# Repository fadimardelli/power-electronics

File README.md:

# Power Electronics

Lab coursework and project for *Power Electronics*, KU Leuven (Campus Group T) — Master's in Electronics-ICT Engineering Technology. The labs are hands-on: build the circuit on a breadboard, characterize it with a bench power supply and oscilloscope, and report the measured behavior against the theoretical prediction.

## Labs

| Lab | Topic | Status |
|---|---|---|
| [`lab-1`](./lab-1) | Thyristor, TRIAC, MOSFET/IGBT switching & clamping circuits | Done |
| [`lab-3`](./lab-3) | Charge pump power supplies (LT1054) & step-down converter (LM2575) | Done |

## Project

| Project | Topic | Status |
|---|---|---|
| [`project`](./project) | DC-DC heavy vehicle converter (24V→12V, 5A) — design, PCB, bench validation | Done |

## Author

Fadi Mardelli — labs done in pairs as noted per lab.

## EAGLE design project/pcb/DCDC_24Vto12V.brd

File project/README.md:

# DC-DC Heavy Vehicle Converter (24 V → 12 V, 5 A)

**Course:** Power Electronics, KU Leuven — Lab responsible: Gert Van Loock
**Team:** Fadi Mardelli, Marios Vlachos

## Goal

Design, build, and characterize a working power-supply prototype from scratch — this is the course's capstone project, distinct from the weekly labs. The brief: pick a converter application from a shortlist (battery chargers, USB supplies, vehicle converters, etc.), design the topology and component values, get a PCB fabricated and soldered, and validate it on the bench against the design targets. A full technical report and a live demo of the working prototype were both required deliverables.

This team's chosen application: a **heavy-vehicle DC-DC converter** converting a 24 V input (regulated over a 20–28 V range) down to a stable 12 V output at up to 5 A, targeting **>90% efficiency**.

## Design

- **Topology:** synchronous buck (step-down) converter — chosen for simplicity and its efficiency advantage over buck-boost or flyback topologies in a pure step-down application.
- **Controller IC:** TI **LM3150** wide-V<sub>IN</sub> synchronous buck controller (6–42 V input range, Constant On-Time control, integrated current limiting / short-circuit / thermal protection).
- **Component values** (R<sub>fb1</sub>/R<sub>fb2</sub>, R<sub>on</sub>, inductor, input/output capacitors, feed-forward and soft-start capacitors, MOSFETs) were hand-calculated from the LM3150 datasheet procedure, then cross-checked against TI's WEBENCH power design tool. Final switching frequency: 500 kHz.
- **PCB:** 2-layer board with short gate-drive traces and a minimized switch-node copper area to control EMI, laid out in EAGLE (exported from WEBENCH, then customized).
- Components were sourced from Farnell (EU stock, single-quantity purchasing).

## Repository contents

```
project/
├── Report_HeavyVehicleConverter.pdf   # Full technical report
├── schematic/DCDC_24Vto12V.sch         # EAGLE schematic
├── pcb/DCDC_24Vto12V.brd               # EAGLE board layout
├── data/Measurements.xlsx              # Raw bench measurement data
└── images/
    ├── PCB_Microscope_Photo.jpg         # Close-up of the assembled board
    ├── Vout_Ripple_200Ohm.JPG           # Output ripple capture
    ├── Vswitch_Switch_Time.JPG          # Switch-node rise-time capture
    ├── static_load_sweep/               # Input-voltage sweep (20–28 V) at 200Ω load
    └── dynamic_load/                    # Load-transient response captures (100 kHz / 250 kHz)
```

The LM2677 datasheet and TI's WEBENCH notice bundled in the original project package are left out, as neither is this team's own work.

## Results

| Metric | Target | Measured |
|---|---|---|
| Output voltage | 12 V | ~12.6–12.7 V, stable across 0–2.1 A load and 20–28 V input |
| Efficiency | >90% | **94.2%** peak (95% simulated) |
| Switching frequency | 500 kHz (design) | ~630 kHz measured |
| Output ripple | — | 34 mV<sub>pp</sub> at 2.5 MHz |
| Switch-node rise time | — | ~17.6 ns |
| IC / MOSFET temperature (5 min, 200 Ω load) | below 165 °C shutdown | 44.1 °C / 40.9 °C |

The converter held continuous-conduction-mode operation at moderate-to-heavy load, with a duty cycle matching theoretical prediction (~53% at V<sub>in</sub> = 24 V). Dynamic load testing (10 V, 100–250 kHz square wave) showed the expected overshoot-on-unload / undershoot-on-load behavior, with some unexpected ringing on overshoot — noted in the report as a possible feedback-compensation improvement for a future revision.

Full derivations, the bill of materials, and the complete measurement set are in the [report](./Report_HeavyVehicleConverter.pdf).

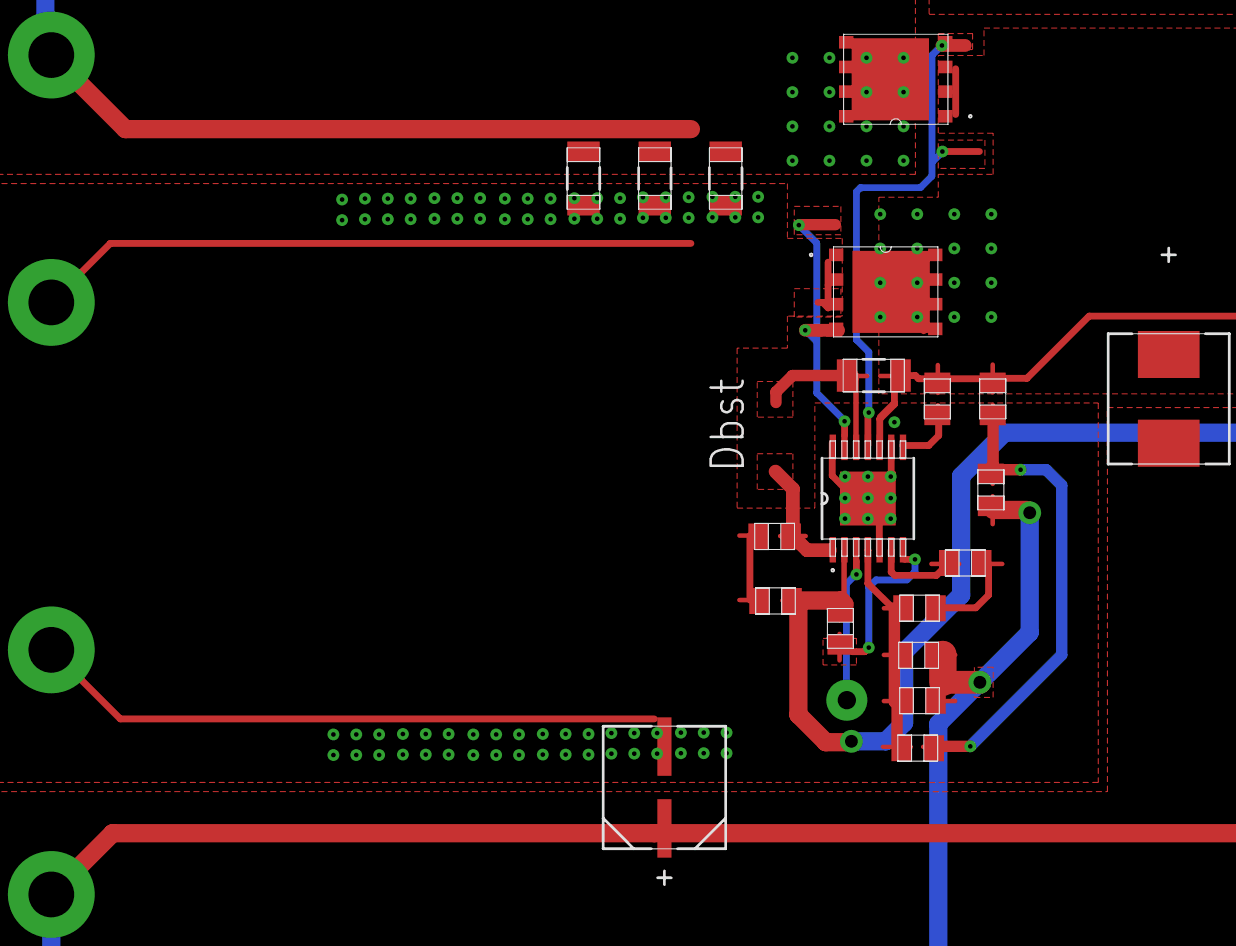
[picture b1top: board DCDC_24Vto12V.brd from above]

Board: 4 copper layers, 25 parts (0 on the bottom side), 14 nets.

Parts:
CAC: 0805
CBST: 1206
CBYP: 0805
CFF: 0805
CIN_1, CIN_2, CIN_3: 1206
COUT: SM_RADIAL_6.3AMM
CR: 0805
CSS: 0805
CVCC: 0805
EN: TP-1502
GND, GND1: TP-1502
L1: IHLP-2525CZ
M1, M2: TRANS_NEXFET_Q5A
RFB1, RFB2: 0805
RLIM: 0805
RON: 0805
RR: 0805
U1: MXA14A
VIN: TP-1502
VOUT: TP-1502

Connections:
0: CBYP.2, CIN_1.2, CIN_2.2, CIN_3.2, COUT.2, CSS.2, CVCC.2, GND.1, GND1.1, M2.1, M2.2, M2.3, RFB1.2, U1.5, U1.9, U1.14, U1.15
1: CBYP.1, CIN_1.1, CIN_2.1, CIN_3.1, M1.5, M1.6, M1.7, M1.8, M1.9, RON.1, U1.2, VIN.1
2: RON.2, U1.7
3: CAC.1, CFF.2, RFB1.1, RFB2.2, U1.4
4: CBST.2, L1.1, M1.1, M1.2, M1.3, M2.5, M2.6, M2.7, M2.8, M2.9, RLIM.1, RR.2, U1.10
5: CFF.1, COUT.1, CR.2, L1.2, RFB2.1, VOUT.1
7: M2.4, U1.13
8: CBST.1, U1.12
9: M1.4, U1.11
10: RLIM.2, U1.8
11: CSS.1, U1.6
12: CVCC.1, U1.1
19: EN.1, U1.3
26: CAC.2, CR.1, RR.1
